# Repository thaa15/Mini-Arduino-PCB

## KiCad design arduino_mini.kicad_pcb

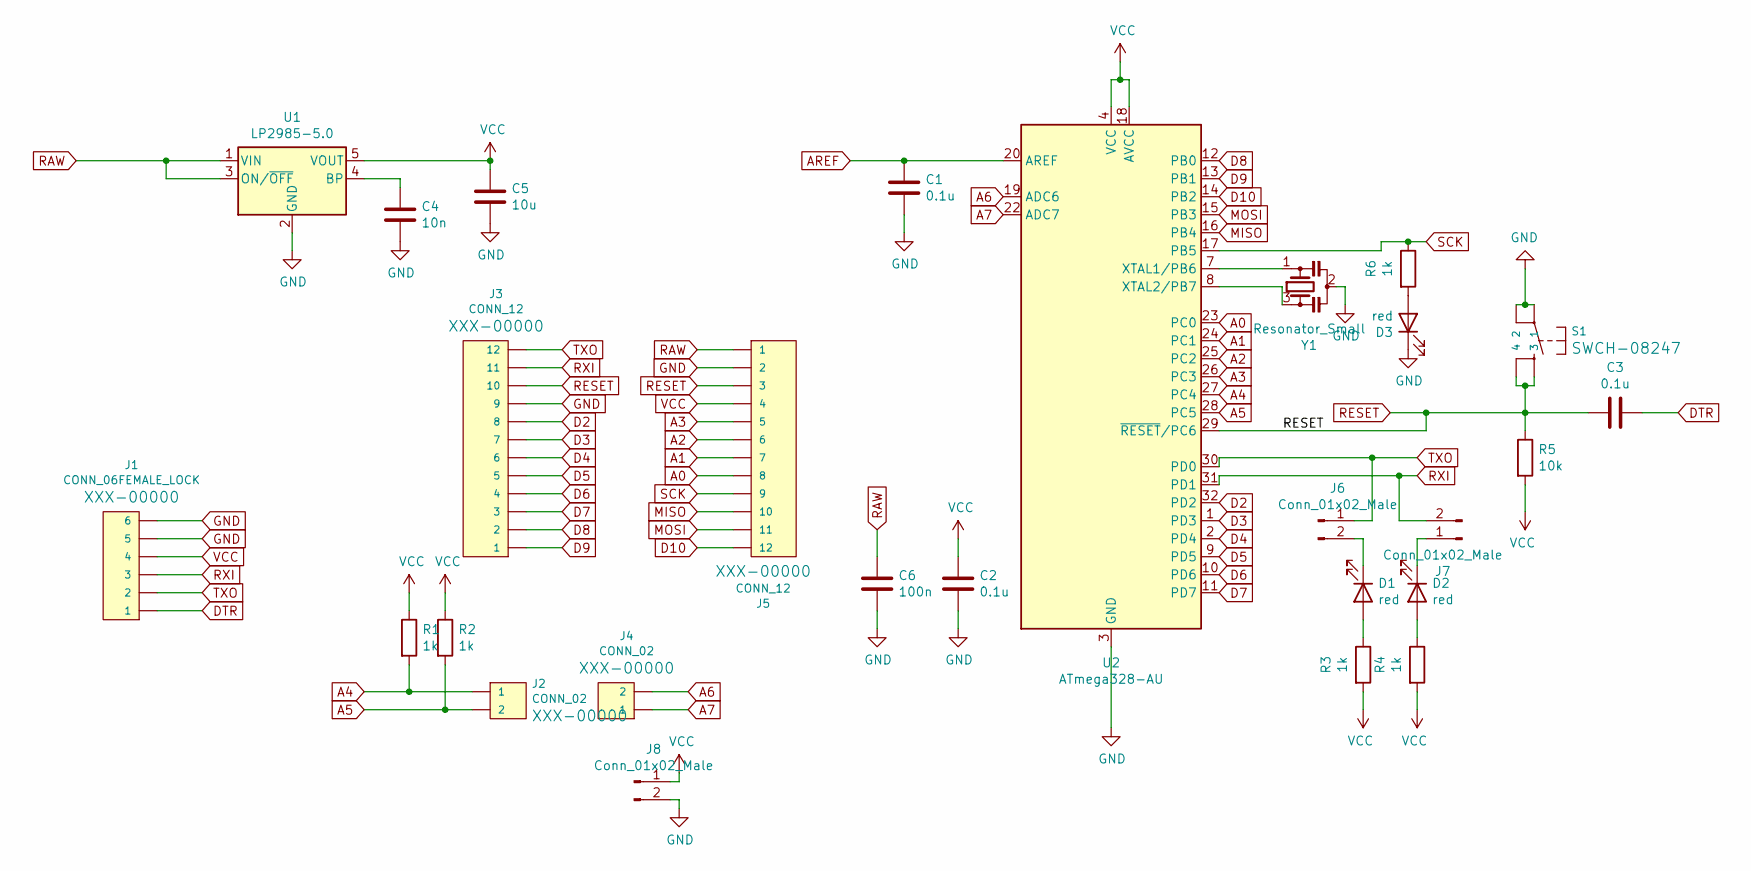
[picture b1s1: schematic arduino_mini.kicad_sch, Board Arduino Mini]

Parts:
C1, C2, C3: 0.1u; C_0603_1608Metric
C4: 10n; C_0603_1608Metric
C5: 10u; C_0603_1608Metric
C6: 100n; C_0603_1608Metric
D1, D2, D3: red; LED_0603_1608Metric
J1: CONN_06FEMALE_LOCK; 1X06_FEMALE_LOCK.010
J2, J4: CONN_02; 1X02
J3, J5: CONN_12; 1X12
J6, J7, J8: Conn_01x02_Male; PinHeader_1x02_P1.00mm_Vertical
R1, R2: 1k; R_0603_1608Metric
R3, R4, R6: 1k; R_0201_0603Metric
R5: 10k; R_0201_0603Metric
S1: MOMENTARY-SWITCH-SPST-2-SMD-5.2MM; TACTILE_SWITCH_SMD_5.2MM
U1: LP2985-5.0; SOT-23-5
U2: ATmega328-AU; TQFP-32_7x7mm_P0.8mm
Y1: Resonator_Small; RESONATOR-SMD-3.2X1.3

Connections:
A0: J5.8, U2.23 (PC0)
A1: J5.7, U2.24 (PC1)
A2: J5.6, U2.25 (PC2)
A3: J5.5, U2.26 (PC3)
A4: J2.1, R1.2, U2.27 (PC4)
A5: J2.2, R2.2, U2.28 (PC5)
A6: J4.2, U2.19 (ADC6)
A7: J4.1, U2.22 (ADC7)
AREF: C1.1, U2.20 (AREF)
D2: J3.8, U2.32 (PD2)
D3: J3.7, U2.1 (PD3)
D4: J3.6, U2.2 (PD4)
D5: J3.5, U2.9 (PD5)
D6: J3.4, U2.10 (PD6)
D7: J3.3, U2.11 (PD7)
D8: J3.2, U2.12 (PB0)
D9: J3.1, U2.13 (PB1)
D10: J5.12, U2.14 (PB2)
DTR: C3.1, J1.1
GND: C1.2, C2.2, C4.2, C5.2, C6.2, D3.1 (K), J1.5, J1.6, J3.9, J5.2, J8.2, S1.1, S1.2, U1.2 (GND), U2.3 (GND), U2.5 (GND), U2.21 (GND), Y1.2
MISO: J5.10, U2.16 (PB4)
MOSI: J5.11, U2.15 (PB3)
unnamed: C4.1, U1.4 (BP)
unnamed: D1.1 (K), J6.2
unnamed: D1.2 (A), R3.1
unnamed: D2.1 (K), J7.1
unnamed: D2.2 (A), R4.1
unnamed: D3.2 (A), R6.2
unnamed: U2.7 (XTAL1/PB6), Y1.1
unnamed: U2.8 (XTAL2/PB7), Y1.3
RAW: C6.1, J5.1, U1.1 (VIN), U1.3 (ON/~OFF)
RESET: C3.2, J3.10, J5.3, R5.1, S1.3, S1.4, U2.29 (~RESET/PC6)
RXI: J1.3, J3.11, J7.2, U2.31 (PD1)
SCK: J5.9, R6.1, U2.17 (PB5)
TXO: J1.2, J3.12, J6.1, U2.30 (PD0)
VCC: C2.1, C5.1, J1.4, J5.4, J8.1, R1.1, R2.1, R3.2, R4.2, R5.2, U1.5 (VOUT), U2.4 (VCC), U2.6 (VCC), U2.18 (AVCC)

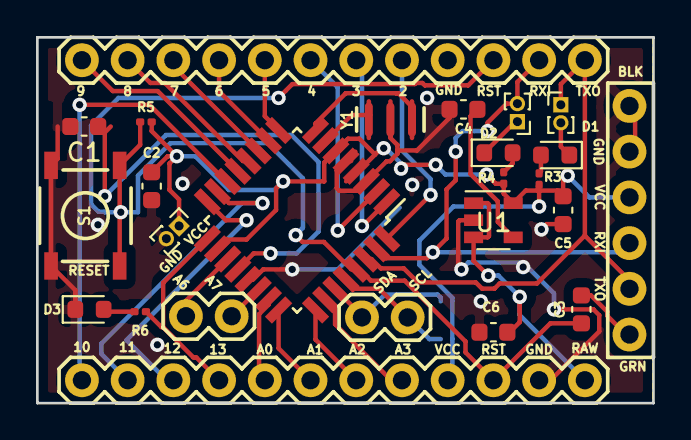
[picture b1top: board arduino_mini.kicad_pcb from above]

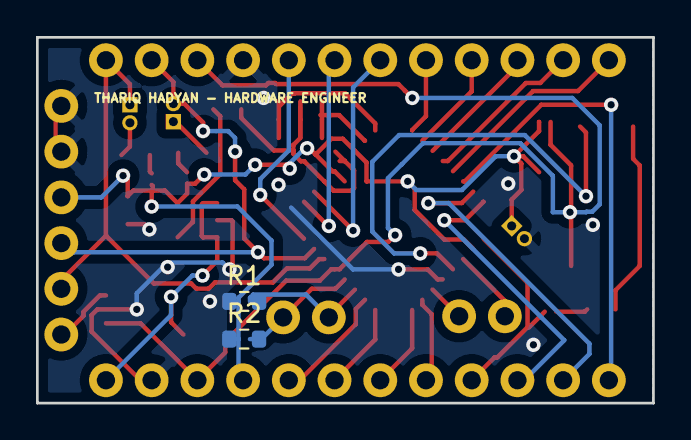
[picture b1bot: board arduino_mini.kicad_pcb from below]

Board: 2 copper layers, 34.2 x 20.3 mm, 27 parts (2 on the bottom side), 36 nets.

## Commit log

2022-05-26 schematics and layout
